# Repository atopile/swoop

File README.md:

# swoop

<div align="center">

</div>

## What is swoop🛫?

With swoop, you can fly remote controlled aircraft with the motion of your hand. It's especially fun when flying FPV because the motion of your remote precisely maps to the aircraft.

## Build your own controller

This project is fully open source and designed with [atopile](https://github.com/atopile/atopile), a new language and compiler to design electronics with code.

**Latest auto-generated artifacts**

[Electronics: Gerbers, Bill of material, position files](https://atopile.s3.amazonaws.com/swoop/electronics/electronics_build_artifacts.zip)

[Firmware](https://atopile.s3.amazonaws.com/swoop/firmware/firmware_build_artifacts.zip)

[3D Files (STL, STEP files in the future)](https://atopile.s3.amazonaws.com/swoop/mechanics/3D_files.zip)

**Atopile code**

The atopile entry point is located [here](https://github.com/atopile/swoop/blob/main/elec/src/swoop.ato). Clone the repository and [install atopile](https://atopile.io/getting-started/) if you'd like to explore further.

## Here is how it works:

The three rotation axis, yaw, pitch, roll of the remote each control the same channel on your aircraft. If you tilt your remote to a certain angle, your aircraft will rotate in that same direction with a certain rotational speed. That's what makes this controller so intuitive to use!
To start using the remote, simply double click the arming button (the larger button). This will zero the controller to the current position and start streaming the control outputs to the receiver.

To control the throttle, which is your aircraft's motor power, simply press the trigger. Inside the controller, a hall sensor precisely keeps track of the trigger position. This makes for a total of four control inputs with yaw, pitch, roll and throttle.

The smaller button on the remote let's you switch the flight mode. Pretty handy to tweak how your aircraft reacts to your control inputs!

Lastly, the remote has an integrated transceiver from the popular open source ExpressLRS project, which makes it compatible with any of their receivers!

## Feature list

Here is what we are planning for this controller:

- Yaw, pitch and roll control angles from the motion of your hand
- Throttle control through the trigger
- Arming button (sets zero position and turn control inputs on/off)
- Flight mode button
- Embedded ExpressLRS transceiver
- Rechargeable over USB-C

## Documentation & Status

We will share documentation once we've made more progress on the project development. For current status, checkout the [product page](https://atopile.io/swoop/).

## Join us!

### Discord

If you are curious about the project, join us on the [atopile discord server](https://discord.gg/nr5V3QRUd3).

### Contributing

If you would like to contribute on atopile, here is what you will need:

For electronics:
- [atopile](https://atopile.io): here is a guide on how to install it: https://atopile.io/getting-started/
- [ExpressLRS](https://www.expresslrs.org): ELRS is an open source long range communication protocol for remote controlled aircraft. If you would like to test the remote, having compatible hardware will help!

For firmware:
- [PlatformIO](https://platformio.org): Cross platform firmware development toolchain
- [CRSF for Arduino](https://github.com/ZZ-Cat/CRSFforArduino): Implementation of the CRSF protocol for arduino. We'll be running this library to stream data from the controller microcontroller to the EzpressLRS module
- [ExpressLRS](https://www.expresslrs.org): ELRS is an open source long range communication protocol for remote controlled aircraft. Their firmware will be flashed on the embedded ESP32S2 module within the controller.

## Happy Flying!

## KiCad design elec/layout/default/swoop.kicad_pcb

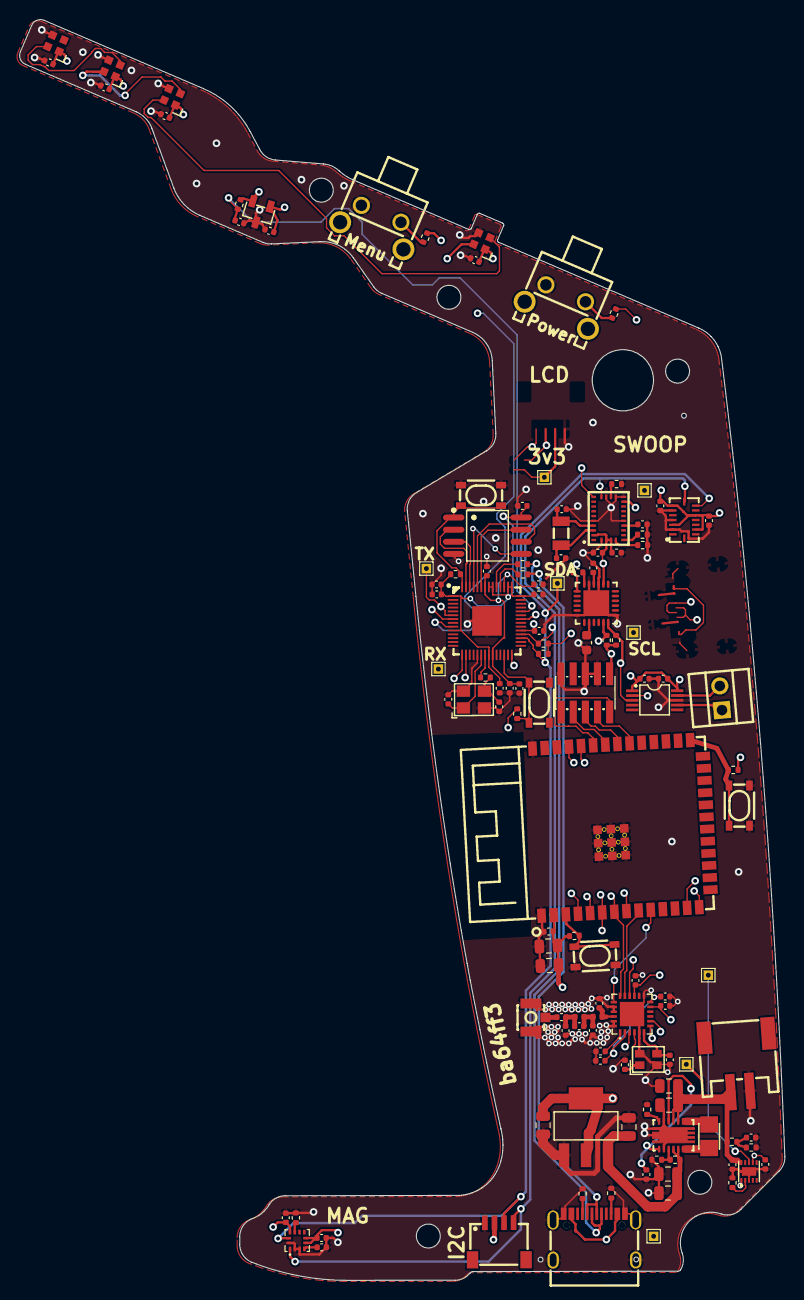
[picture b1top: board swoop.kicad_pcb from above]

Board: 4 copper layers, 80.0 x 131.9 mm, 128 parts (0 on the bottom side), 78 nets.

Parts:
C1, C2, C26, C27: 50V 18pF C0G ±5% 0402 Multilayer Ceramic Capacito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; C0402
C3, C4, C5, C6, C7, C9, C10, C11, C19, C22, C23, C25, C28, C29, C30, C32, C34, C35, C41, C42, C50, C51, C52, C53, C54, C55: 16V 100nF X7R ±10% 0402 Multilayer Ceramic Capaci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; C0402
C8, C12, C13, C14, C24, C33, C56, C57: 25V 1uF X5R ±10% 0402 Multilayer Ceramic Capacito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; C0402
C15, C16, C17, C18, C20, C21, C36, C37: 25V 10uF X5R ±10% 0805 Multilayer Ceramic Capacit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; C0805
C31: 50V 2.2nF X7R ±10% 0603 Multilayer Ceramic Capaci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; C0603
C38, C39: 50V 12pF C0G ±5% 0402 Multilayer Ceramic Capacito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; C0402
C40: 50V 470nF X5R ±10% 0402 Multilayer Ceramic Capaci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; C0402
C43, C44: 50V 10nF X7R ±10% 0402 Multilayer Ceramic Capacit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; C0402
C45: 50V 0.8pF 0402 Multilayer Ceramic Capacitors MLCC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; C0402
C46, C47: 50V 1.2pF C0G 0402 Multilayer Ceramic Capacitors 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; C0402
C48: 50V 0.5pF C0G 0402 Multilayer Ceramic Capacitors 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; C0402
C49: 50V 100pF C0G ±5% 0402 Multilayer Ceramic Capacit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; C0402
J1: CONN-SMD_4P-P1.00_SM04B-SRSS-TB-LF-SN
L1: IND-SMD_L2.5-W2.0_WPN252012H
L2, L3: L0402
R1, R2, R14, R15, R16, R17, R18, R19, R21, R22, R25, R26: 62.5mW Thick Film Resistors 50V ±100ppm/℃ ±1% 10k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; R0402
R3, R20: 62.5mW Thick Film Resistors 50V ±100ppm/℃ ±1% 1kΩ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; R0402
R4, R5: 62.5mW Thick Film Resistors 50V ±100ppm/℃ ±1% 27Ω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; R0402
R6, R7: 62.5mW Thick Film Resistors 50V ±100ppm/℃ ±1% 2kΩ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; R0402
R8: 100mW Thick Film Resistors ±100ppm/℃ ±1% 1.07kΩ 0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; R0402
R9: 62.5mW Thick Film Resistors 50V ±100ppm/℃ ±1% 698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; R0402
R10: 62.5mW Thick Film Resistors 50V ±1% ±200ppm/℃ 105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; R0402
R11: 62.5mW Thick Film Resistors 50V ±100ppm/℃ ±1% 1MΩ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; R0402
R12: 62.5mW Thick Film Resistors 50V ±100ppm/℃ ±1% 16.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; R0402
R13: 62.5mW Thick Film Resistors 50V ±100ppm/℃ ±1% 17.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; R0402
R23, R24: 62.5mW Thick Film Resistors 50V ±100ppm/℃ ±1% 4.7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; R0402
R27: 62.5mW Thick Film Resistors ±100ppm/℃ ±1% 3.24kΩ 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; R0402
U1: LQFN-56_L7.0-W7.0-P0.4-EP
U2, U3, U25, U29: KEY-SMD_4P-L4.2-W3.2-P2.20-LS4.6
U4: OSC-SMD_4P-L3.2-W2.5-BL
U5: SOIC-8_L5.3-W5.3-P1.27-LS8.0-BL
U6, U7, U8, U9, U10, U15, U16, U17, U18: TestPoint_THTPad_1.0x1.0mm_Drill0.5mm
U11: CONN-SMD_P2.00_S2B-PH-SM4-TB-LF-SN
U12: WSON-10_L2.0-W2.0-P0.40-BL-EP
U13: VSON-14_L4.0-W3.0-P0.50-BL-EP_TI_DSJ
U14: SOT-223-3_L6.5-W3.4-P2.30-LS7.0-BR
U19: LGA-28_L5.2-W3.8-P0.50-BL
U20: FC-135R_L3.2-W1.5
U21: LGA-16_L4.5-W3.0-P0.50-BL
U22: QFN-24_L4.0-W4.0-P0.50-BL-EP2.7
U23: LGA-12_L2.0-W2.0-P0.50-BL
U24: WIRELM-SMD_ESP32-S3-WROOM-1
U26: QFN-24_L4.0-W4.0-P0.50-BL-EP2.6
U27: OSC-SMD_4P-L2.0-W1.6-BL
U28: IPEX-SMD_BWIPX-1-001E
U30: HDR-SMD_10P-P1.27-V-M-R2-C5-LS5.3
U31: USB-C-SMD_KH-TYPE-C-16P
U32, U33, U34, U35: LED-SMD_4P-L2.0-W2.0-BR
U36, U37: SW-TH_TS-1093C-A7B3-D1
U38: SOT-23-3_L2.9-W1.3-P0.95-LS2.4-BR
U39: VSSOP-10_L3.0-W3.0-P0.50-LS4.9-BL
U40: CONN-TH_DB125-2.54-2P-GN

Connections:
c1: C32.1, U23.4
cap: C25.1, U19.9
cc1: R23.1, U31.A5
cc2: R24.1, U31.B5
com3: R14.1, U19.17
cpout: C31.2, U22.20
dm: R5.1, U31.A7, U31.B7
dp: R4.2, U31.A6, U31.B6
gnd: C1.2, C2.2, C3.2, C4.2, C5.2, C6.2, C7.2, C8.2, C9.2, C10.2, C11.2, C12.2, C13.2, C14.2, C15.2, C16.2, C17.2, C18.2, C19.2, C20.2, C21.2, C22.2, C23.2, C24.2, C25.2, C26.2, C27.2, C28.2, C29.2, C30.1, C31.1, C32.2, C33.2, C34.2, C35.2, C36.2, C37.2, C38.2, C39.2, C40.2, C41.2, C42.2, C43.2, C44.2, C45.2, C46.2, C47.2, C50.2, C51.2, C52.2, C53.2, C54.2, C55.2, C56.2, C57.2, J1.1, R8.2, R10.2, R11.2, R13.2, R14.2, R15.2, R16.2, R20.2, R23.2, R24.2, U1.19, U1.57, U2.3, U2.4, U3.3, U3.4, U4.2, U4.4, U5.4, U11.1, U12.3, U12.11, U13.2, U13.13, U13.15, U14.1, U19.2, U19.10, U19.15, U19.16, U19.18, U19.25, U21.2, U21.4, U21.6, U22.1, U22.9, U22.11, U22.18, U22.25, U23.2, U23.3, U23.12, U24.1, U24.40, U24.41, U25.3, U25.4, U26.5, U26.13, U26.20, U26.21, U26.23, U26.24, U26.25, U27.2, U27.4, U28.2, U28.3, U29.3, U29.4, U30.3, U30.5, U30.9, U31.1, U31.2, U31.3, U31.4, U31.A1, U31.A12, U31.B1, U31.B12, U32.3, U33.3, U34.3, U35.3, U36.2, U37.2, U38.3, U39.8
imu.lis3mdltr.ic-miso: R20.1, U23.9
interrupt: R17.1, U22.12
io4: U24.4, U26.7
io5: U24.5, U26.8
io6: U24.6, U26.3
io7: U24.7, U26.18
io15: U24.8, U26.16
io16: U24.9, U26.17
io17: U24.10, U26.19
ios.hall_effect.ic-vcc: R27.1, U38.2
ios.led1.ic-vcc: U32.2, U33.4
ios.led2.ic-vcc: U33.2, U34.4
ios.led3.ic-vcc: U34.2, U35.4
iset: R8.1, U12.2
l1: L1.1, U13.8, U13.9
l2: L1.2, U13.6, U13.7
micro-vcc: U1.36, U10.1, U19.14
micro-vcc-1: R25.2, U1.15, U36.1
micro-vcc-2: R26.2, U1.16, U37.1
micro-vcc-3: U1.9, U32.4
micro-vcc-4: C55.1, R27.2, U1.38
micro-vcc-5: U1.28, U12.8, U18.1
micro.micro-cs-1: R2.2, U1.56, U3.1, U3.2, U5.1
micro.micro-io0: U1.53, U5.5
micro.micro-io1: U1.55, U5.2
micro.micro-io2: U1.54, U5.3
micro.micro-io3: U1.51, U5.7
micro.micro-sck-1: U1.52, U5.6
micro.micro.micro-vcc: C9.1, C10.1, C11.1, C12.1, U1.23, U1.45, U1.50
micro.micro.osc.osc-out: C2.1, R3.2, U4.3
n: U39.9, U40.2
p: U39.7, U40.1
power_supply-vcc: C13.1, U12.1, U12.7, U15.1, U31.A4, U31.A9, U31.B4, U31.B9
power_supply.battery-vcc: C14.1, C15.1, C16.1, R12.1, U11.2, U12.10, U13.10, U13.11, U17.1
power_supply.battery_voltage_sensor-out: C22.1, R12.2, R13.1
power_supply.buckboost-vcc: C17.1, C18.1, C20.1, R9.1, U13.4, U13.5, U14.3
power_supply.buckboost.tps_buck_boost.feedback_div-out: R9.2, R10.1, U13.3
power_supply.buckboost.tps_buck_boost.ic-pg: R11.1, U13.14
ps0: R15.1, U19.6
ps1: R16.1, U19.5
radio._micro.ic-en: R21.2, U24.3, U25.1, U25.2
radio._micro.ic-io0: R22.2, U24.27, U29.1, U29.2
radio._radio.decoupling_cap-gnd: C49.2, U28.1
radio._radio.ic-vcc: C44.1, U26.1
radio._radio.ic-vcc-1: C40.1, C43.1, U26.2, U26.12
radio._radio.ic-vcc-2: C45.1, L2.1, U26.22
radio._radio.matching_circuit-vcc: C46.1, C48.1, L2.2, L3.1
radio._radio.pi_filter-vcc: C47.1, C48.2, C49.1, L3.2
regout: C30.2, U22.10
run: R1.2, U1.26, U2.1, U2.2
rx: U1.7, U9.1, U24.37
scl: J1.4, R7.1, R19.1, U1.32, U6.1, U19.19, U21.8, U22.23, U23.1, U39.2
sda: J1.3, R6.1, R18.1, U1.31, U7.1, U19.20, U21.9, U22.24, U23.11, U39.3
sdo2: U21.10, U21.15
tck: U24.32, U30.4
tdi: U24.34, U30.8
tdo: U24.33, U30.6
tms: U24.35, U30.2
tx: U1.6, U8.1, U24.36
usb_dm: R5.2, U1.46
usb_dp: R4.1, U1.47
vcc: C3.1, C4.1, C5.1, C6.1, C7.1, C8.1, C21.1, C23.1, C24.1, C28.1, C29.1, C33.1, C34.1, C35.1, C36.1, C37.1, C41.1, C42.1, C50.1, C51.1, C52.1, C53.1, C54.1, C56.1, C57.1, J1.2, R1.1, R2.1, R6.2, R7.2, R17.2, R18.2, R19.2, R21.1, R22.1, R25.1, R26.1, U1.1, U1.10, U1.22, U1.33, U1.42, U1.43, U1.44, U1.48, U1.49, U5.8, U14.2, U14.4, U16.1, U19.3, U19.4, U19.28, U21.3, U21.7, U21.11, U22.8, U22.13, U23.5, U23.6, U23.10, U24.2, U26.11, U26.15, U30.1, U32.1, U33.1, U34.1, U35.1, U38.1, U39.1, U39.10
vina: C19.1, U13.1, U13.12
xin: C1.1, U1.20, U4.1
xin32: C26.1, U19.27, U20.1
xout: R3.1, U1.21
xout32: C27.1, U19.26, U20.2
xta: C38.1, U26.4, U27.1
xtb: C39.1, U26.6, U27.3

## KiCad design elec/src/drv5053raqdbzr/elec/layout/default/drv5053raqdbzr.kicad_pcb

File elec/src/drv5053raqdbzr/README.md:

# drv5053raqdbzr

Wooohooo a new package!

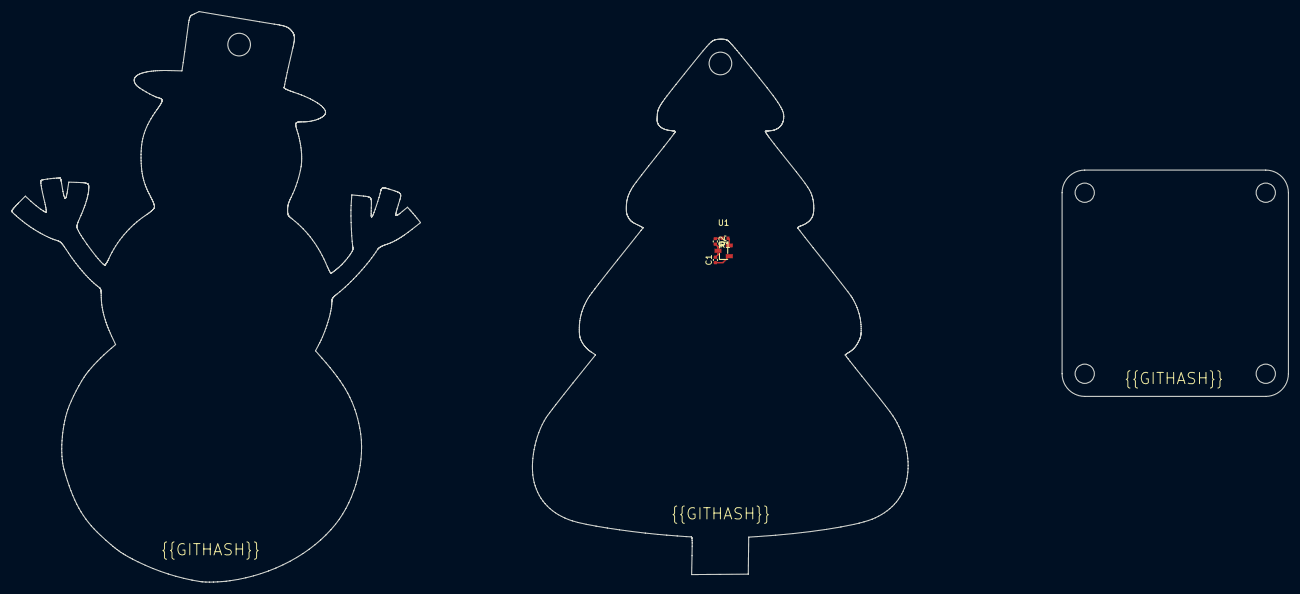
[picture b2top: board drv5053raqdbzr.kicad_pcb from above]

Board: 2 copper layers, 66.4 x 94.6 mm, 4 parts (0 on the bottom side), 4 nets.

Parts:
C1, C2: 16V 100nF X7R ±10% 0402 Multilayer Ceramic Capaci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; C0402
R1: 62.5mW Thick Film Resistors ±100ppm/℃ ±1% 3.24kΩ 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; R0402
U1: SOT-23-3_L2.9-W1.3-P0.95-LS2.4-BR

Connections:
gnd: C1.2, C2.2, U1.3
ic-vcc: R1.1, U1.2
vcc: C1.1, U1.1
vcc-1: C2.1, R1.2

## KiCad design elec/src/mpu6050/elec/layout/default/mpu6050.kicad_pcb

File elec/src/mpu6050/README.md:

# mpu6050

Wooohooo a new package!

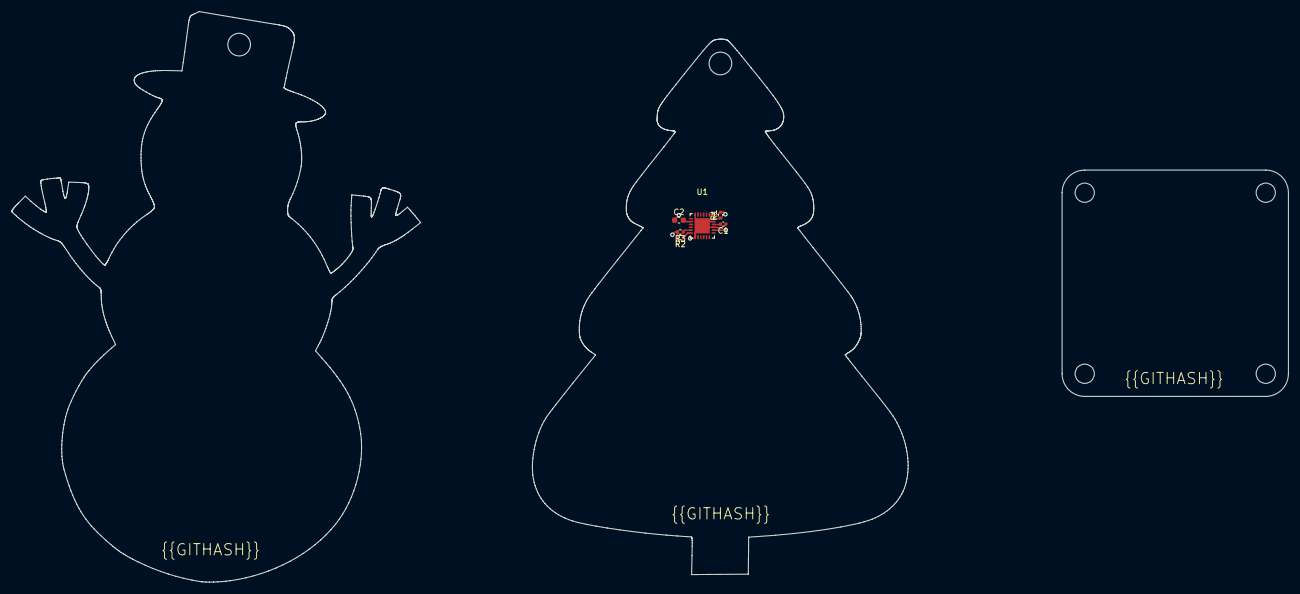
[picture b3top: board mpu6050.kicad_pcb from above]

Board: 2 copper layers, 66.4 x 94.6 mm, 6 parts (0 on the bottom side), 7 nets.

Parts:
C1: 16V 100nF X7R ±10% 0402 Multilayer Ceramic Capaci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; C0402
C2: 50V 2.2nF X7R ±10% 0603 Multilayer Ceramic Capaci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; C0603
R1, R2, R3: 62.5mW Thick Film Resistors ±100ppm/℃ ±1% 10kΩ 04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; R0402
U1: QFN-24_L4.0-W4.0-P0.50-BL-EP2.7

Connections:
cpout: C2.2, U1.20
gnd-1: C1.1, C2.1, U1.1, U1.9, U1.11, U1.18, U1.25
interrupt: R1.1, U1.12
regout: C1.2, U1.10
scl: R3.1, U1.23
sda: R2.1, U1.24
vcc: R1.2, R2.2, R3.2, U1.8, U1.13

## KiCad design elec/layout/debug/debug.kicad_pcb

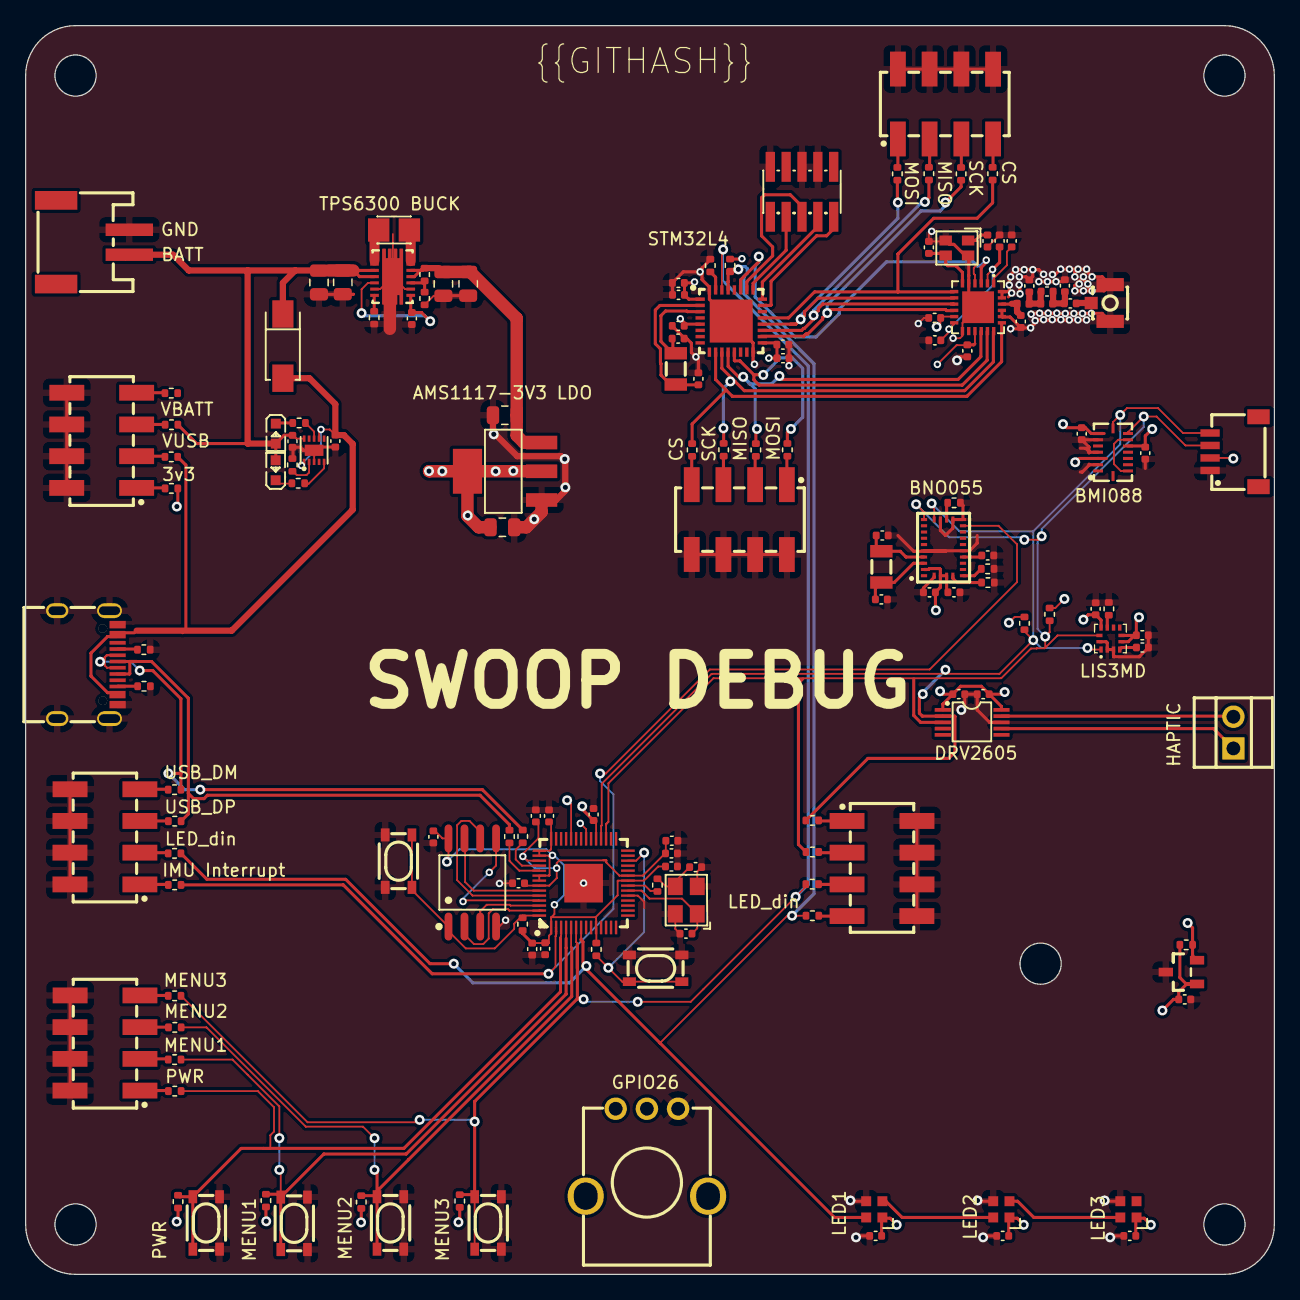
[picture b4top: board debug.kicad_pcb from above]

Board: 4 copper layers, 100.0 x 100.0 mm, 150 parts (0 on the bottom side), 103 nets.

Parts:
C1, C2: 50V 20pF C0G ±5% 0402 Multilayer Ceramic Capacito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; C0402
C3, C4, C5, C6, C7, C9, C10, C11, C19, C22, C24, C27, C28, C29, C31, C33, C35, C42, C43, C51, C52, C53, C54: 16V 100nF X7R ±10% 0402 Multilayer Ceramic Capaci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; C0402
C8, C12, C13, C14, C23, C30, C34, C55, C56: 25V 1uF X5R ±10% 0402 Multilayer Ceramic Capacito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; C0402
C15, C16, C17, C18, C20, C21: 25V 10uF X5R ±10% 0805 Multilayer Ceramic Capacit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; C0805
C25, C26: 50V 22pF C0G ±5% 0402 Multilayer Ceramic Capacito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; C0402
C32: 10V 4.7uF X5R ±20% 0402 Multilayer Ceramic Capaci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; C0402
C36, C44, C45: 50V 10nF X7R ±10% 0402 Multilayer Ceramic Capacit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; C0402
C37, C38: 50V 13pF C0G ±2% 0402 Multilayer Ceramic Capacito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; C0402
C39, C40: 50V 11pF C0G ±5% 0402 Multilayer Ceramic Capacito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; C0402
C41: 10V 470nF X5R ±10% 0402 Multilayer Ceramic Capaci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; C0402
C46, C47, C48, C49: 50V 1pF C0G 0402 Multilayer Ceramic Capacitors ML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; C0402
C50: 50V 100pF C0G ±5% 0402 Multilayer Ceramic Capacit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; C0402
D1: SMA_L4.2-W2.6-LS5.3-RD
J1: CONN-SMD_4P-P1.00_SM04B-SRSS-TB-LF-SN
L1: IND-SMD_L2.5-W2.0_WPN252012H
L2, L3: L0402
LED1, LED2: LED0603-RD
R1, R2, R6, R7, R14, R15, R16, R19, R22, R23, R24, R25: 62.5mW Thick Film Resistors ±100ppm/℃ ±1% 10kΩ 04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; R0402
R3, R17, R26, R27, R28, R29, R30, R31, R32, R33, R34, R35, R36, R37, R38, R39, R40, R41, R42, R43, R44, R45, R46, R47, R48, R49, R50: 62.5mW Thick Film Resistors ±100ppm/℃ ±1% 1kΩ 040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; R0402
R4, R5: 62.5mW Thick Film Resistors ±100ppm/℃ ±1% 27kΩ 04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; R0402
R8: 62.5mW Thick Film Resistors ±100ppm/℃ ±1% 510Ω 04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; R0402
R9: 62.5mW Thin Film Resistor ±0.5% ±25ppm/℃ 110Ω 040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; R0402
R10: 62.5mW Thick Film Resistors ±100ppm/℃ ±1% 82Ω 040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; R0402
R11: 100mW Thick Film Resistors ±5% ±200ppm/℃ 1.1MΩ 04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; R0402
R12: 62.5mW Thick Film Resistors ±100ppm/℃ ±1% 180kΩ 0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; R0402
R13: 62.5mW Thick Film Resistors ±100ppm/℃ ±1% 1MΩ 040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; R0402
R18: 62.5mW Thick Film Resistors ±100ppm/℃ ±1% 330Ω 04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; R0402
R20, R21: 62.5mW Thick Film Resistors ±100ppm/℃ ±1% 5.1kΩ 0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; R0402
U1: LQFN-56_L7.0-W7.0-P0.4-EP
U2: OSC-SMD_4P-L3.2-W2.5-BL
U3: SOIC-8_L5.3-W5.3-P1.27-LS8.0-BL
U4, U5, U24, U25, U26, U27: KEY-SMD_4P-L4.2-W3.2-P2.20-LS4.6
U6: CONN-SMD_P2.00_S2B-PH-SM4-TB-LF-SN
U7: WSON-10_L2.0-W2.0-P0.40-BL-EP
U8: VSON-14_L4.0-W3.0-P0.50-BL-EP_TI_DSJ
U9: SOT-223-3_L6.5-W3.4-P2.30-LS7.0-BR
U10: LGA-28_L5.2-W3.8-P0.50-BL
U11, U15: FC-135R_L3.2-W1.5
U12: LGA-16_L4.5-W3.0-P0.50-BL
U13: LGA-12_L2.0-W2.0-P0.50-BL
U14: UFQFPN-32_L5.0-W5.0-P0.50-TL-EP3.5
U16: QFN-24_L4.0-W4.0-P0.50-BL-EP2.6
U17: OSC-SMD_4P-L2.0-W1.6-BL
U18: IPEX-SMD_BWIPX-1-001E
U19: HDR-SMD_10P-P1.27-V-M-R2-C5-LS5.3
U20: USB-C-SMD_KH-TYPE-C-16P
U21, U22, U23: LED-SMD_4P-L2.0-W2.0-BR
U28: SOT-23-3_L2.9-W1.3-P1.90-LS2.4-BR-CW
U29: VSSOP-10_L3.0-W3.0-P0.50-LS4.9-BL
U30: CONN-TH_DB125-2.54-2P-GN
U31, U32, U33, U34, U35, U36: HDR-SMD_8P-P2.54-V-M-R2-C4-LS7.4
U37: RES-ADJ-TH_RK09K1130AJ3

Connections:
_1: R27.2, U31.1
_1-1: R31.2, U32.1
_1-2: R35.2, U33.1
_1-3: R39.2, U34.1
_1-4: R43.2, U35.1
_1-5: R47.2, U36.1
_3: R28.2, U31.3
_3-1: R32.2, U32.3
_3-2: R36.2, U33.3
_3-3: R40.2, U34.3
_3-4: R44.2, U35.3
_3-5: R48.2, U36.3
_5: R29.2, U31.5
_5-1: R33.2, U32.5
_5-2: R37.2, U33.5
_5-3: R41.2, U34.5
_5-4: R45.2, U35.5
_5-5: R49.2, U36.5
_7-1: R30.2, U31.7
_7-2: R34.2, U32.7
_7-3: R38.2, U33.7
_7-4: R42.2, U34.7
_7-5: R46.2, U35.7
_7-6: R50.2, U36.7
c1: C29.1, U13.4
cap: C24.1, U10.9
cathode: LED1.1, R9.1
cathode-1: LED2.1, R10.1
cc1: R20.1, U20.A5
cc2: R21.1, U20.B5
com3: R14.1, U10.17
cs: R7.2, U1.56, U3.1, U5.1, U5.2
cs-2: R46.1, U14.10, U16.19
dm: R5.1, R34.1, U20.A7, U20.B7
dp: R4.2, R33.1, U20.A6, U20.B6
gnd: C1.2, C2.2, C3.2, C4.2, C5.2, C6.2, C7.2, C8.2, C9.2, C10.2, C11.2, C12.2, C13.2, C14.2, C15.2, C16.2, C17.2, C18.2, C19.2, C20.2, C21.2, C22.2, C23.2, C24.2, C25.2, C26.2, C27.2, C28.2, C29.2, C30.2, C31.2, C32.2, C33.2, C34.2, C35.2, C36.2, C37.2, C38.2, C39.2, C40.2, C41.2, C42.2, C43.2, C44.2, C45.2, C46.2, C47.2, C48.2, C51.2, C52.2, C53.2, C54.2, C55.2, C56.2, J1.1, R8.2, R12.2, R13.2, R14.2, R15.2, R16.2, R17.2, R19.2, R20.2, R21.2, U1.19, U1.57, U2.2, U2.4, U3.4, U4.3, U4.4, U5.3, U5.4, U6.1, U7.3, U7.11, U8.2, U8.13, U8.15, U9.1, U10.2, U10.10, U10.15, U10.16, U10.18, U10.25, U12.2, U12.4, U12.6, U13.2, U13.3, U13.12, U14.16, U14.32, U14.33, U16.5, U16.13, U16.20, U16.21, U16.23, U16.24, U16.25, U17.2, U17.4, U18.2, U18.3, U19.3, U19.5, U19.9, U20.1, U20.2, U20.3, U20.4, U20.A1, U20.A12, U20.B1, U20.B12, U21.3, U22.3, U23.3, U24.3, U24.4, U25.3, U25.4, U26.3, U26.4, U27.3, U27.4, U28.2, U29.8, U31.2, U31.4, U31.6, U31.8, U32.2, U32.4, U32.6, U32.8, U33.2, U33.4, U33.6, U33.8, U34.2, U34.4, U34.6, U34.8, U35.2, U35.4, U35.6, U35.8, U36.2, U36.4, U36.6, U36.8, U37.1
gnd-4: R9.2, U7.5
gnd-5: R10.2, U7.8
gnd-10: C50.2, U18.1
io: U1.35, U37.2
io0: U1.53, U3.5
io1: U1.55, U3.2
io2: U1.54, U3.3
io3: U1.51, U3.7
io-1: U14.27, U16.3
io-2: C46.1, L2.1, U16.22
iset: R8.1, U7.2
l1: L1.1, U8.8, U8.9
l2: L1.2, U8.6, U8.7
miso-1: R17.1, U13.9
miso-2: R44.1, U14.12, U16.16
mosi-1: R43.1, U14.13, U16.17
n: U29.9, U30.2
out: C2.1, R3.2, U2.3
out-1: R11.2, R12.1, U8.3
p: U29.7, U30.1
pc14_osc32_in: C37.1, U14.2, U15.1
pc15_osc32_out: C38.1, U14.3, U15.2
pg: R13.1, U8.14
ph3_boot0: R19.1, U14.31
ps0: R15.1, U10.6
ps1: R16.1, U10.5
run: R6.2, U1.26, U4.1, U4.2
sck: U1.52, U3.6
sck-2: R45.1, U14.11, U16.18
scl: J1.4, R2.1, R27.1, U1.32, U10.19, U12.8, U13.1, U29.2
sda: J1.3, R1.1, R28.1, U1.31, U10.20, U12.9, U13.11, U29.3
sdo2: U12.10, U12.15
tck: U14.24, U19.4
tdi: U14.25, U19.8
tdo: U14.26, U19.6
tms: U14.23, U19.2
usb_dm: R5.2, U1.46
usb_dp: R4.1, U1.47
vcc: C3.1, C4.1, C5.1, C6.1, C7.1, C8.1, C21.1, C22.1, C23.1, C27.1, C28.1, C30.1, C31.1, C32.1, C33.1, C34.1, C35.1, C36.1, C42.1, C43.1, C51.1, C52.1, C53.1, C54.1, C55.1, C56.1, J1.2, R1.2, R2.2, R6.1, R7.1, R18.2, R22.1, R23.1, R24.1, R25.1, R26.1, R39.1, U1.1, U1.10, U1.22, U1.33, U1.42, U1.43, U1.44, U1.48, U1.49, U3.8, U9.2, U9.4, U10.3, U10.4, U10.28, U12.3, U12.7, U12.11, U13.5, U13.6, U13.10, U14.1, U14.5, U14.17, U16.11, U16.15, U21.1, U22.1, U23.1, U28.1, U29.1, U29.10, U37.3
vcc-1: R25.2, R29.1, R38.1, U1.6, U14.30, U27.1, U27.2
vcc-2: R18.1, R30.1, R32.1, U1.7, U14.29, U21.4
vcc-3: R31.1, U1.2, U10.14
vcc-4: R22.2, R35.1, U1.3, U24.1, U24.2
vcc-5: R23.2, R36.1, U1.4, U25.1, U25.2
vcc-6: R24.2, R37.1, U1.5, U26.1, U26.2
vcc-7: R26.2, U1.38, U28.3
vcc-8: C9.1, C10.1, C11.1, C12.1, U1.23, U1.45, U1.50
vcc-9: C13.1, D1.2, R40.1, U7.1, U7.7, U20.A4, U20.A9, U20.B4, U20.B9
vcc-10: C14.1, C15.1, C16.1, D1.1, LED1.2, LED2.2, R41.1, U6.2, U7.10, U8.10, U8.11
vcc-13: C17.1, C18.1, C20.1, R11.1, U8.4, U8.5, U9.3
vcc-14: R49.1, U14.18, U16.10
vcc-15: R48.1, U14.19, U16.9
vcc-16: R47.1, U14.20, U16.8
vcc-17: R50.1, U14.21, U16.7
vcc-19: C45.1, U16.1
vcc-20: C41.1, C44.1, U16.2, U16.12
vcc-22: C47.1, C49.1, L2.2, L3.1
vcc-23: C48.1, C49.2, C50.1, L3.2
vcc-25: U21.2, U22.4
vcc-26: U22.2, U23.4
vina: C19.1, U8.1, U8.12
xin: C1.1, U1.20, U2.1
xin32: C25.1, U10.27, U11.1
xout: R3.1, U1.21
xout32: C26.1, U10.26, U11.2
xta: C39.1, U16.4, U17.1
xtb: C40.1, U16.6, U17.3

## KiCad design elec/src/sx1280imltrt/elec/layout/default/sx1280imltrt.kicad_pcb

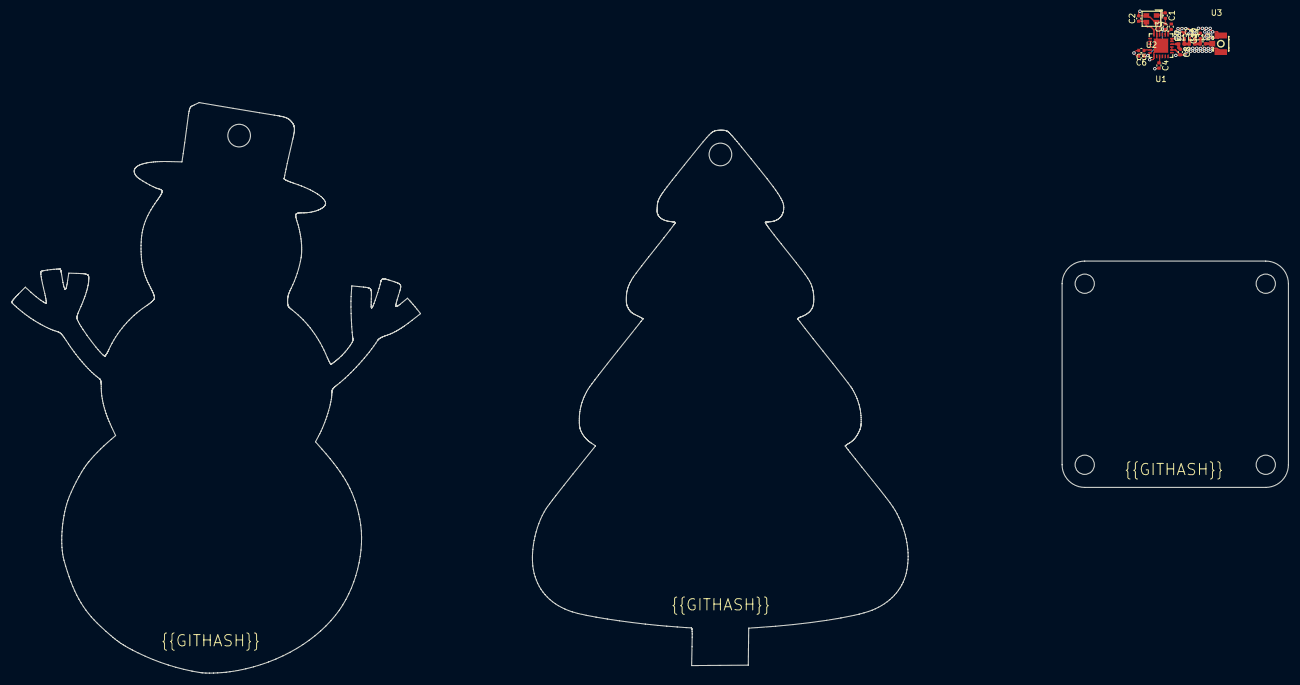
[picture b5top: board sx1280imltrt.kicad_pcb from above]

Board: 2 copper layers, 17 parts (0 on the bottom side), 10 nets.

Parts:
C1, C2: 50V 11pF C0G ±5% 0402 Multilayer Ceramic Capacito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; C0402
C3: 10V 470nF X5R ±10% 0402 Multilayer Ceramic Capaci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; C0402
C4, C5: Multilayer Ceramic Capacitors MLCC - SMD/SMT 100n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; C0402
C6, C7: 50V 10nF X7R ±10% 0402 Multilayer Ceramic Capacit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; C0402
C8, C9, C10, C11: 50V 1pF C0G 0402 Multilayer Ceramic Capacitors ML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; C0402
C12: 50V 100pF C0G ±5% 0402 Multilayer Ceramic Capacit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; C0402
L1, L2: L0402
U1: QFN-24_L4.0-W4.0-P0.50-BL-EP2.6
U2: OSC-SMD_4P-L2.0-W1.6-BL
U3: IPEX-SMD_BWIPX-1-001E

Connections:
gnd: C1.2, C2.2, C3.2, C4.2, C5.2, C6.2, C7.2, C8.2, C9.2, C10.2, U1.5, U1.13, U1.20, U1.21, U1.23, U1.24, U1.25, U2.2, U2.4, U3.2, U3.3
gnd-3: C12.2, U3.1
io: C8.1, L1.1, U1.22
vcc: C7.1, U1.1
vcc-1: C3.1, C6.1, U1.2, U1.12
vcc-2: C4.1, C5.1, U1.11, U1.15
vcc-4: C9.1, C11.1, L1.2, L2.1
vcc-5: C10.1, C11.2, C12.1, L2.2
xta: C1.1, U1.4, U2.1
xtb: C2.1, U1.6, U2.3

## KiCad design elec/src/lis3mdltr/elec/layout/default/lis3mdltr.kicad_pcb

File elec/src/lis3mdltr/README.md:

# lis3mdltr

Wooohooo a new package!

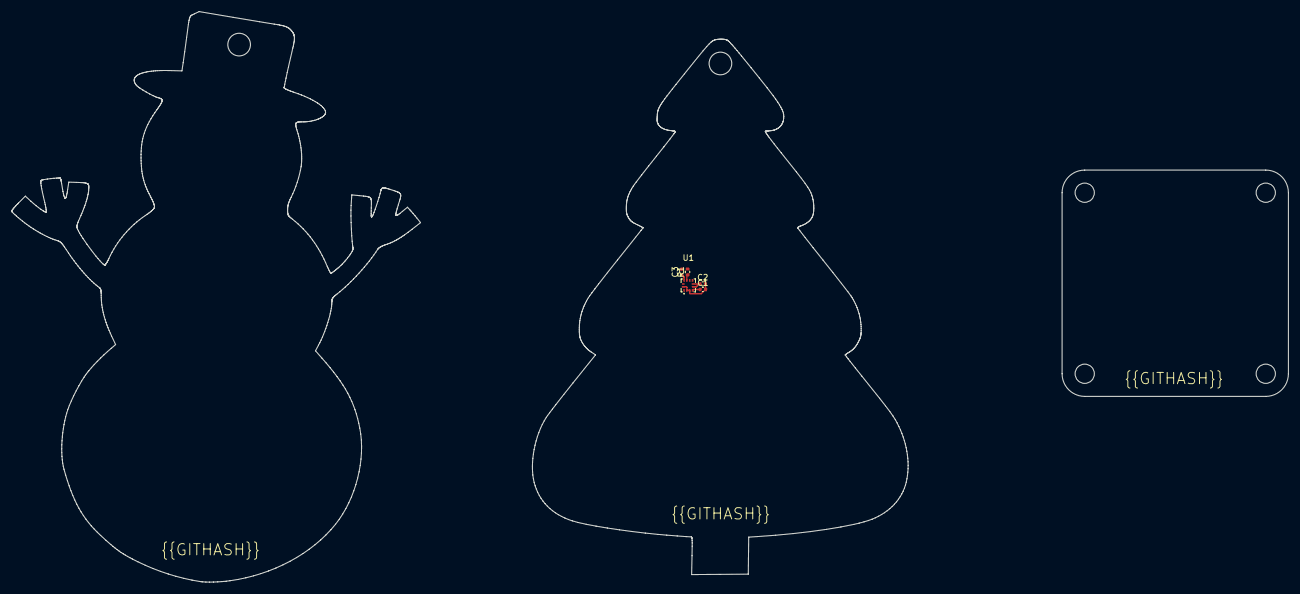
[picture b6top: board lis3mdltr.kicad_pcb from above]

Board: 2 copper layers, 66.4 x 94.6 mm, 5 parts (0 on the bottom side), 4 nets.

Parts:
C1, C3: Multilayer Ceramic Capacitors MLCC - SMD/SMT 100n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; C0402
C2: Multilayer Ceramic Capacitors MLCC - SMD/SMT 1uF 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; C0402
R1: Chip Resistor - Surface Mount 1.1KOhms ±5% 1/16W 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; R0402
U1: LGA-12_L2.0-W2.0-P0.50-BL

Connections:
c1: C1.1, U1.4
gnd: C1.2, C2.2, C3.2, R1.2, U1.2, U1.3, U1.12
miso: R1.1, U1.9
vcc: C2.1, C3.1, U1.5, U1.6, U1.10

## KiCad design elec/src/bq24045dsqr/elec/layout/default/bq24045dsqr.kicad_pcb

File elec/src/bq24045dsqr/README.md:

# bq24045dsqr

Wooohooo a new package!

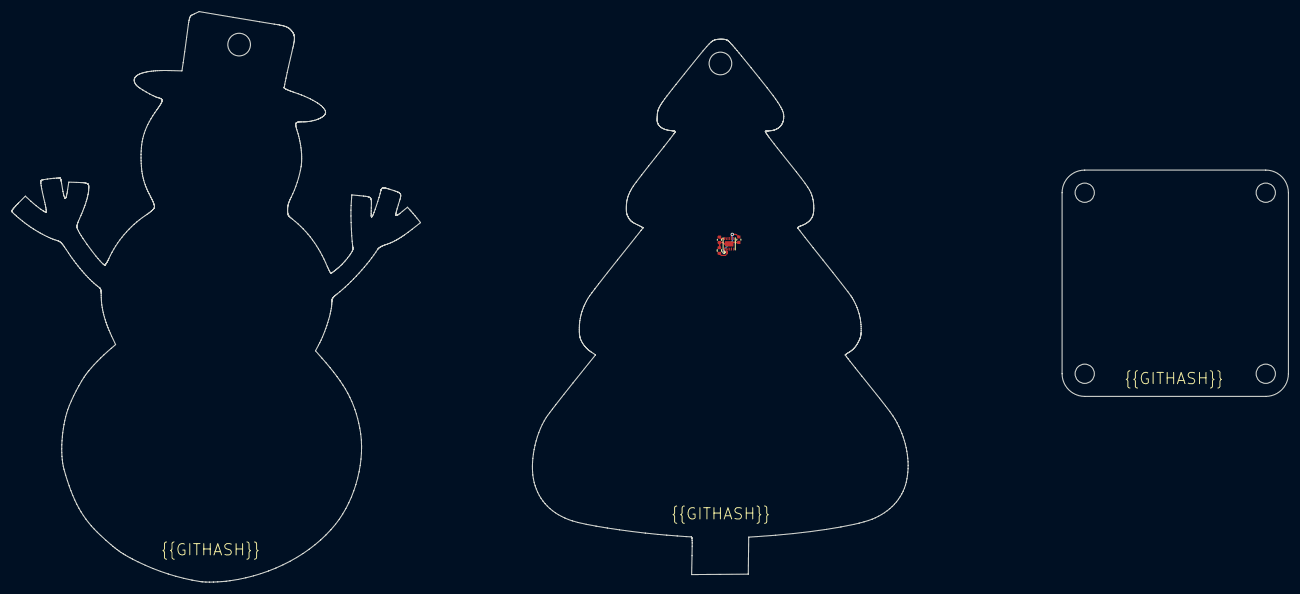
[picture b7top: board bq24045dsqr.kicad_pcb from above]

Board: 2 copper layers, 66.4 x 94.6 mm, 4 parts (0 on the bottom side), 4 nets.

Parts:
C1, C2: 25V 1uF X5R ±10% 0402 Multilayer Ceramic Capacito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; C0402
R1: 100mW Thick Film Resistors ±100ppm/℃ ±1% 604Ω 040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; R0402
U1: WSON-10_L2.0-W2.0-P0.40-BL-EP

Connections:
ic-gnd: C1.2, C2.2, R1.2, U1.3, U1.11
ic-vcc: C1.1, U1.1, U1.7
ic-vcc-1: C2.1, U1.10
iset: R1.1, U1.2

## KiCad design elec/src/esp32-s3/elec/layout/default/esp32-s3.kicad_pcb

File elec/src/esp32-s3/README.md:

## Overview

The ESP32-S3 is a powerful, versatile microcontroller designed for IoT applications. It features dual-core Xtensa LX7 processors, Wi-Fi and Bluetooth 5 connectivity, rich I/O capabilities, and enhanced security features, making it ideal for smart home devices, wearable electronics, and automated systems requiring efficient processing and wireless communication.

## Usage Example

```
import ESP32 from "esp32/esp32.ato"
import Power from "generics/interfaces.ato"

module my_project:
   power3v3 = new Power
   micro = new ESP32
   micro.power ~ power3v3

```

## Features
Power interface: 3.3V input
SPI interface: 4-wire SPI
I2C interface
JTAG interface

## Contributing
Contribute to this package using pull requests.

## License
This battery connector module is provided under the MIT License.

## Contact
For further inquiries or support, please contact me at narayan@atopile.io.

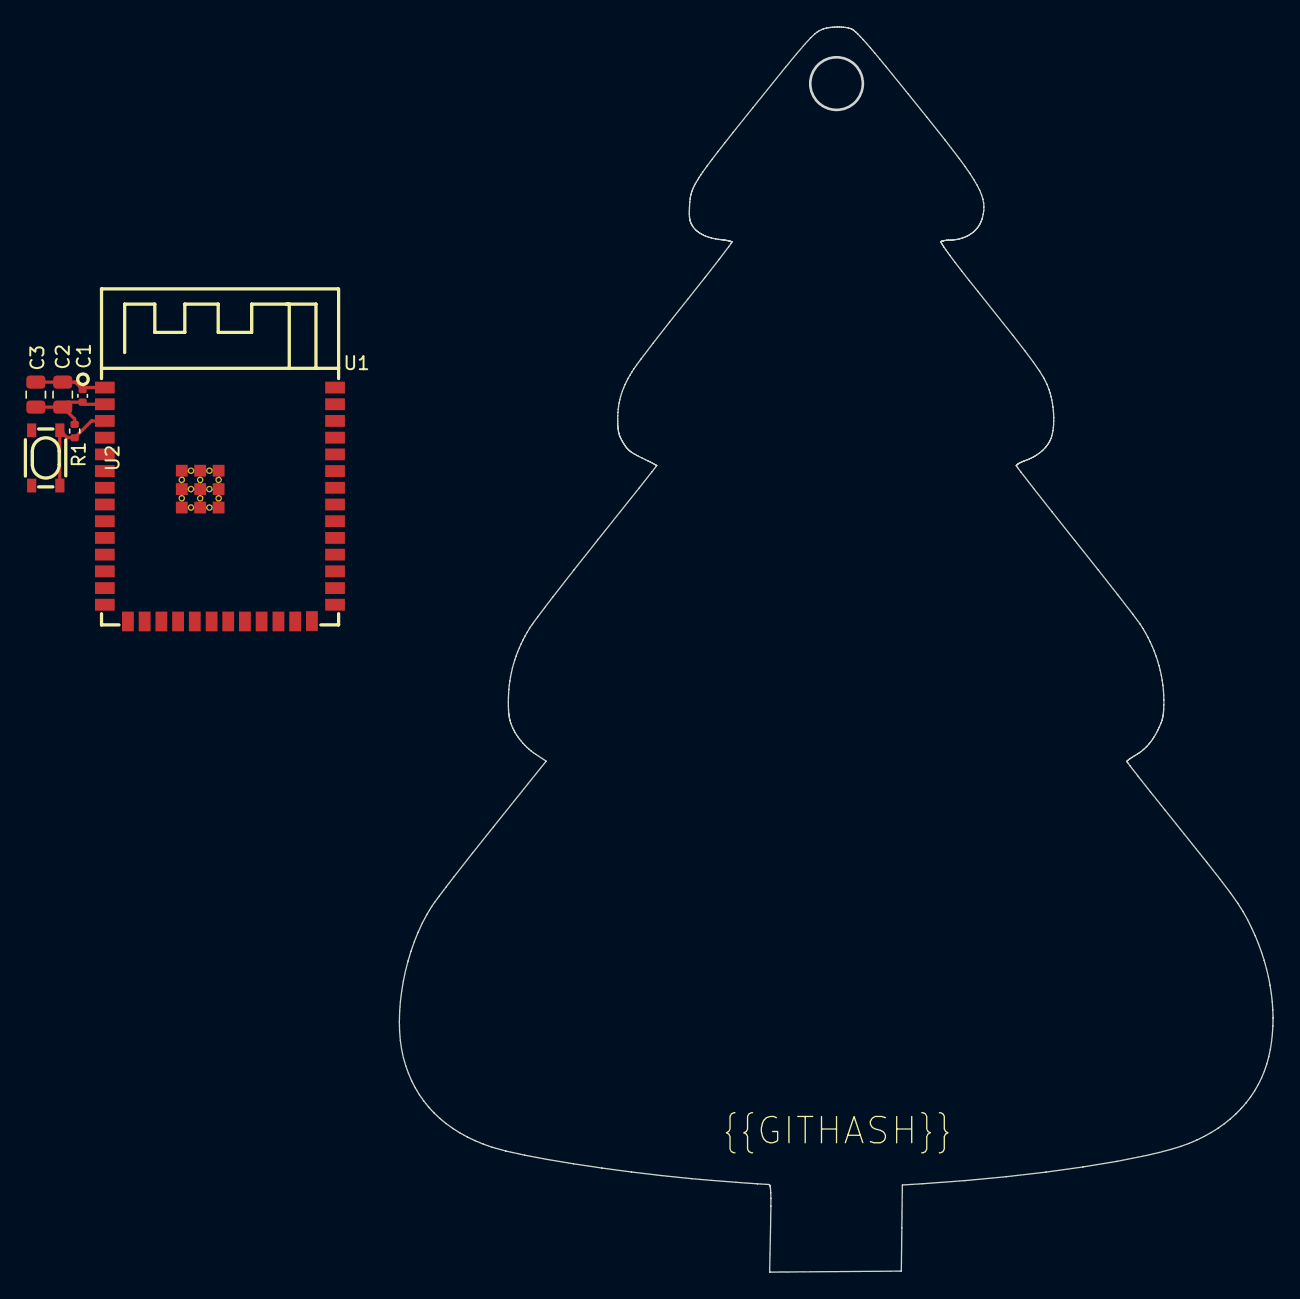
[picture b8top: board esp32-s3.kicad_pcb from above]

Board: 2 copper layers, 66.4 x 94.6 mm, 6 parts (0 on the bottom side), 3 nets.

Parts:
C1: 16V 100nF X7R ±10% 0402 Multilayer Ceramic Capaci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; C0402
C2, C3: 25V 10uF X5R ±10% 0805 Multilayer Ceramic Capacit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; C0805
R1: 62.5mW Thick Film Resistors ±100ppm/℃ ±1% 10kΩ 04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; R0402
U1: WIRELM-SMD_ESP32-S3-WROOM-1
U2: KEY-SMD_4P-L4.2-W3.2-P2.20-LS4.6

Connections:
en: R1.2, U1.3, U2.1, U2.2
ic-gnd: C1.2, C2.2, C3.2, U1.1, U1.40, U1.41, U2.3, U2.4
vcc: C1.1, C2.1, C3.1, R1.1, U1.2

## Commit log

2024-02-15 Configure project
2024-02-17 checkin
2024-02-17 ios cleanup
2024-02-17 layout 80% complete
2024-02-17 merge
2024-02-18 layout 95%
2024-02-18 layout complete
2024-02-18 updated dependencies
2024-02-18 fix typo in deps
2024-02-18 updating deps
2024-02-29 added equation support
2024-03-01 Deps installed and hello world running
2024-03-01 Get the popped IMU running
2024-03-01 Theoretically working 2-chip solution
2024-03-02 Try BNO086 FW
2024-03-02 BNO086 working!
2024-03-07 Update radio to use ESP32 rather than STM32
2024-03-19 updating workflow with manual trigger
2024-03-19 fixing esp32 import
2024-03-19 cleanup
2024-03-19 testing new CI with kicad8
2024-03-19 fixing path
2024-03-19 adding default build
2024-03-27 minor cleanup
2024-03-30 added functionality for buttons
2024-03-31 added power button behaviour
2024-04-02 quating it up
2024-04-02 switch the sensor orientation
2024-04-17 adding deps locally
2024-04-17 remove lib deps
2024-04-18 update fw
2024-04-19 still missing ypr control angle generation
2024-04-19 cleanup and comments
2024-04-20 add the ypr angle extraction
2024-04-25 fix the viewer positions
2024-04-25 fix the viewer positions (#18)
2024-04-25 update the readme
2024-04-25 add image
2024-04-25 add pics to readme
2024-04-25 add product page
2024-04-25 add discord
2024-04-25 Update to readme (#19)
2024-04-26 merging in layouts
2024-04-26 cleaner commit
2024-04-26 Update README.md (#21)
2024-04-26 remove test container from ci job
2024-04-26 fix missing V in physical
2024-04-26 increase i_q for it to solve
2024-04-27 merging in layouts (#20)
    * merging in layouts
    * cleaner commit
    * remove test container from ci job
    * fix missing V in physical
    * increase i_q for it to solve
    ---------
2024-04-27 firmware_flow_diagram.drawio
2024-04-29 swoop_data_flow_diagram.drawio
2024-04-29 change file name
2024-04-29 compress
2024-04-29 Process flow diagram (#22)
2024-04-29 Bringup of the quaternion math (#17)
2024-05-21 fix parts on sx1280
2024-05-21 add comment
2024-05-21 Fix MPNs on sx1280 front end (#23)
    * fix parts on sx1280
    * add comment
2024-05-30 add ci to swoop
2024-05-30 FastLED leading to build failure
2024-05-30 update readme with badge
2024-05-30 change the badge name
2024-05-30 update the tiles
2024-05-30 change badge
2024-05-30 center the badges
2024-05-30 add hw ci
2024-05-30 add stl
2024-05-30 add step
2024-05-30 try again
2024-06-01 update the hw CI
2024-06-01 update file name
2024-06-01 fix tab
2024-06-02 platformio: force FastLED to exactly version 3.6
    From 3.7 on there is an issue with the addLeds function producing `Error: invalid offset, value too big` compile errors.
    See https://github.com/earlephilhower/arduino-pico/discussions/1649
2024-06-02 Move LED logic into separate class
    The button dependency should still move out.
2024-06-03 without steps, it's not gonna work
2024-06-03 upload the firmware artifacts
2024-06-03 update the shields
2024-06-03 revert changes to main
2024-06-03 remove clutter
2024-06-04 add s3 push
2024-06-04 run whenever
2024-06-04 add s3 push to fw and to 3d
2024-06-04 fix 3d yml
2024-06-04 zip things up
2024-06-04 add artifacts folder
2024-06-04 move artifacts
2024-06-04 fix 3d and firmware
2024-06-04 update readme with build artifacts
2024-06-04 Add firmware + 3D files CI (#26)
2024-06-04 change fw zipped files
2024-06-22 Add firmware readme with Windows Setup instructions
2024-06-23 Firmware: revise readme and add instructions for Mac
2024-07-06 Add copy of matrix library from PX4
    including a script to automatically update it in the future.
2024-07-08 Temporary tests of the rotation math implementation
2024-07-08 Temporary calculations test
    Not ran yet on hardware
2024-07-12 fix the quat order
2024-07-12 add quaternion zeroing
2024-07-22 add ppm and rcmapper
